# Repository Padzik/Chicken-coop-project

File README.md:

# Chicken coop project ("Kurník 21. století")
Chicken coop controller board (Eagle schematics) + arduino SW (for arduino and attiny + modified dependent libraries)

## HW comment
* Arduino nano + Attiny85 (for battery protection)
* LCD with nice user friendly menu
* External temp probe + automatic fan controller
* Set your GPS location (via menu) and you are ready to go! (actual Sunrise and Sunset is automaticly calculated every day + you can add user delay time)
* Build in Buzzer for Pavlov reflex (one minute before door open/close starts beeping)
* RTC has build in automatic SW correction (cheap RTCs can be running up to 30s late every day) + automatic summer/winter time
* External LED for door status + Data output via Serial 
* H-bridge + motor from screwdriver for door opening (build in safety mechanism for sensor failure) Door position is controlled by Magnetic Sensor Window Alarm Switch (I have tried mechanical and also Hall-sensor switches, but this one is more realible)
* It has also manual override function for doors
* Solar panel / main voltage power supply + UPS 6V battery (up to 2 days of running on battery backup) + Hibernation mode for low backup voltage on battery
* Double sided PCB can be easily prepared at home conditions (I have made many prototype versions)

Inspired by [Arduino chicken project by user RobotChicken](http://www.instructables.com/id/Arduino-Chicken-Coop-Controller/)

## Photos

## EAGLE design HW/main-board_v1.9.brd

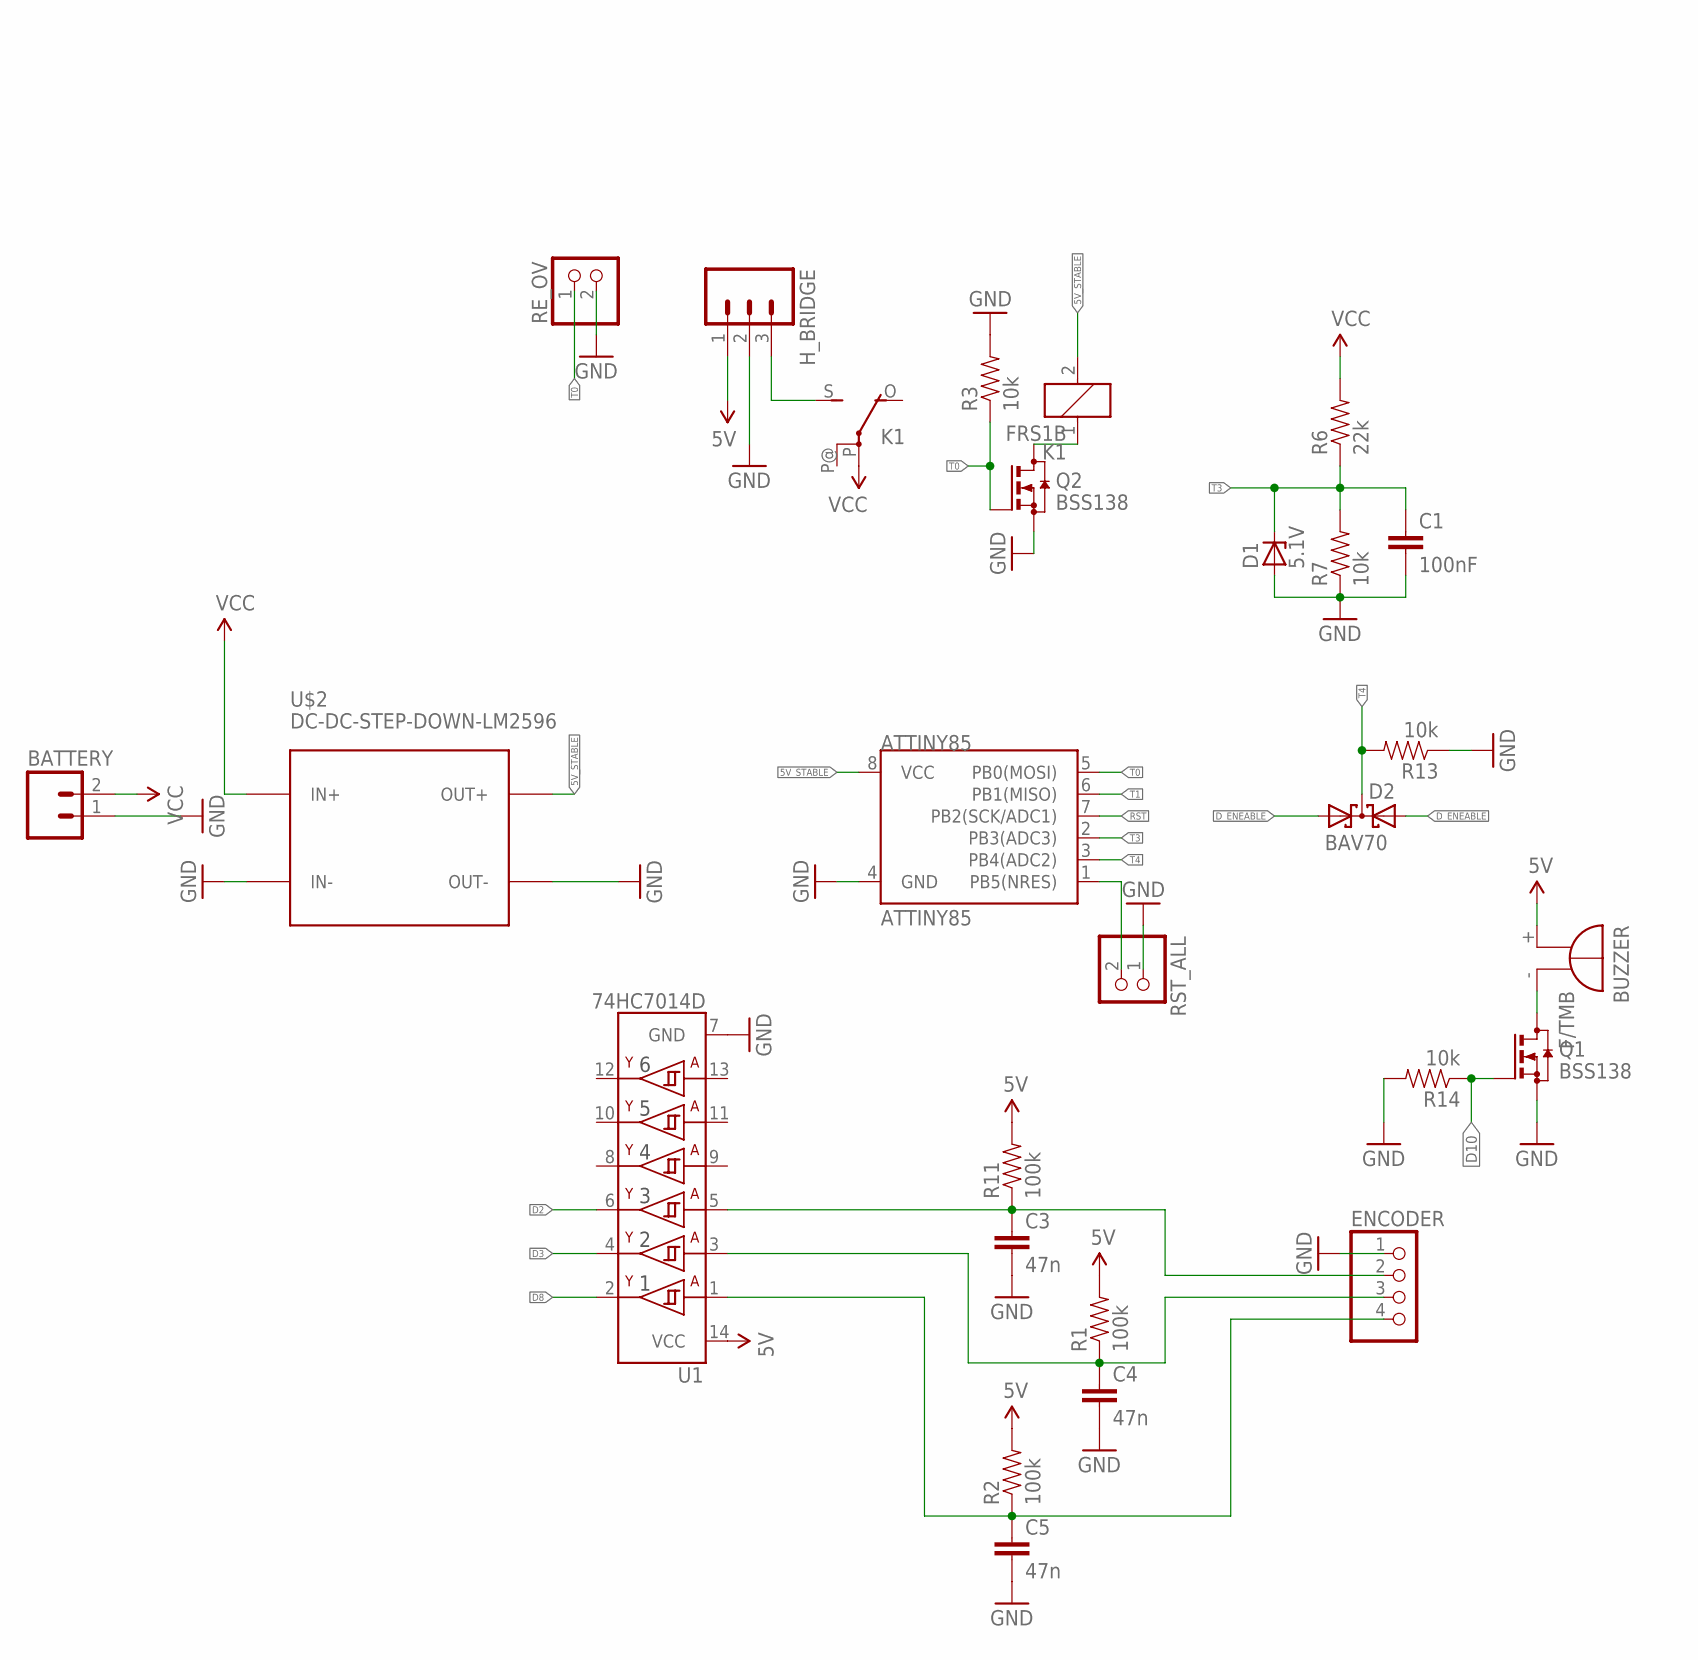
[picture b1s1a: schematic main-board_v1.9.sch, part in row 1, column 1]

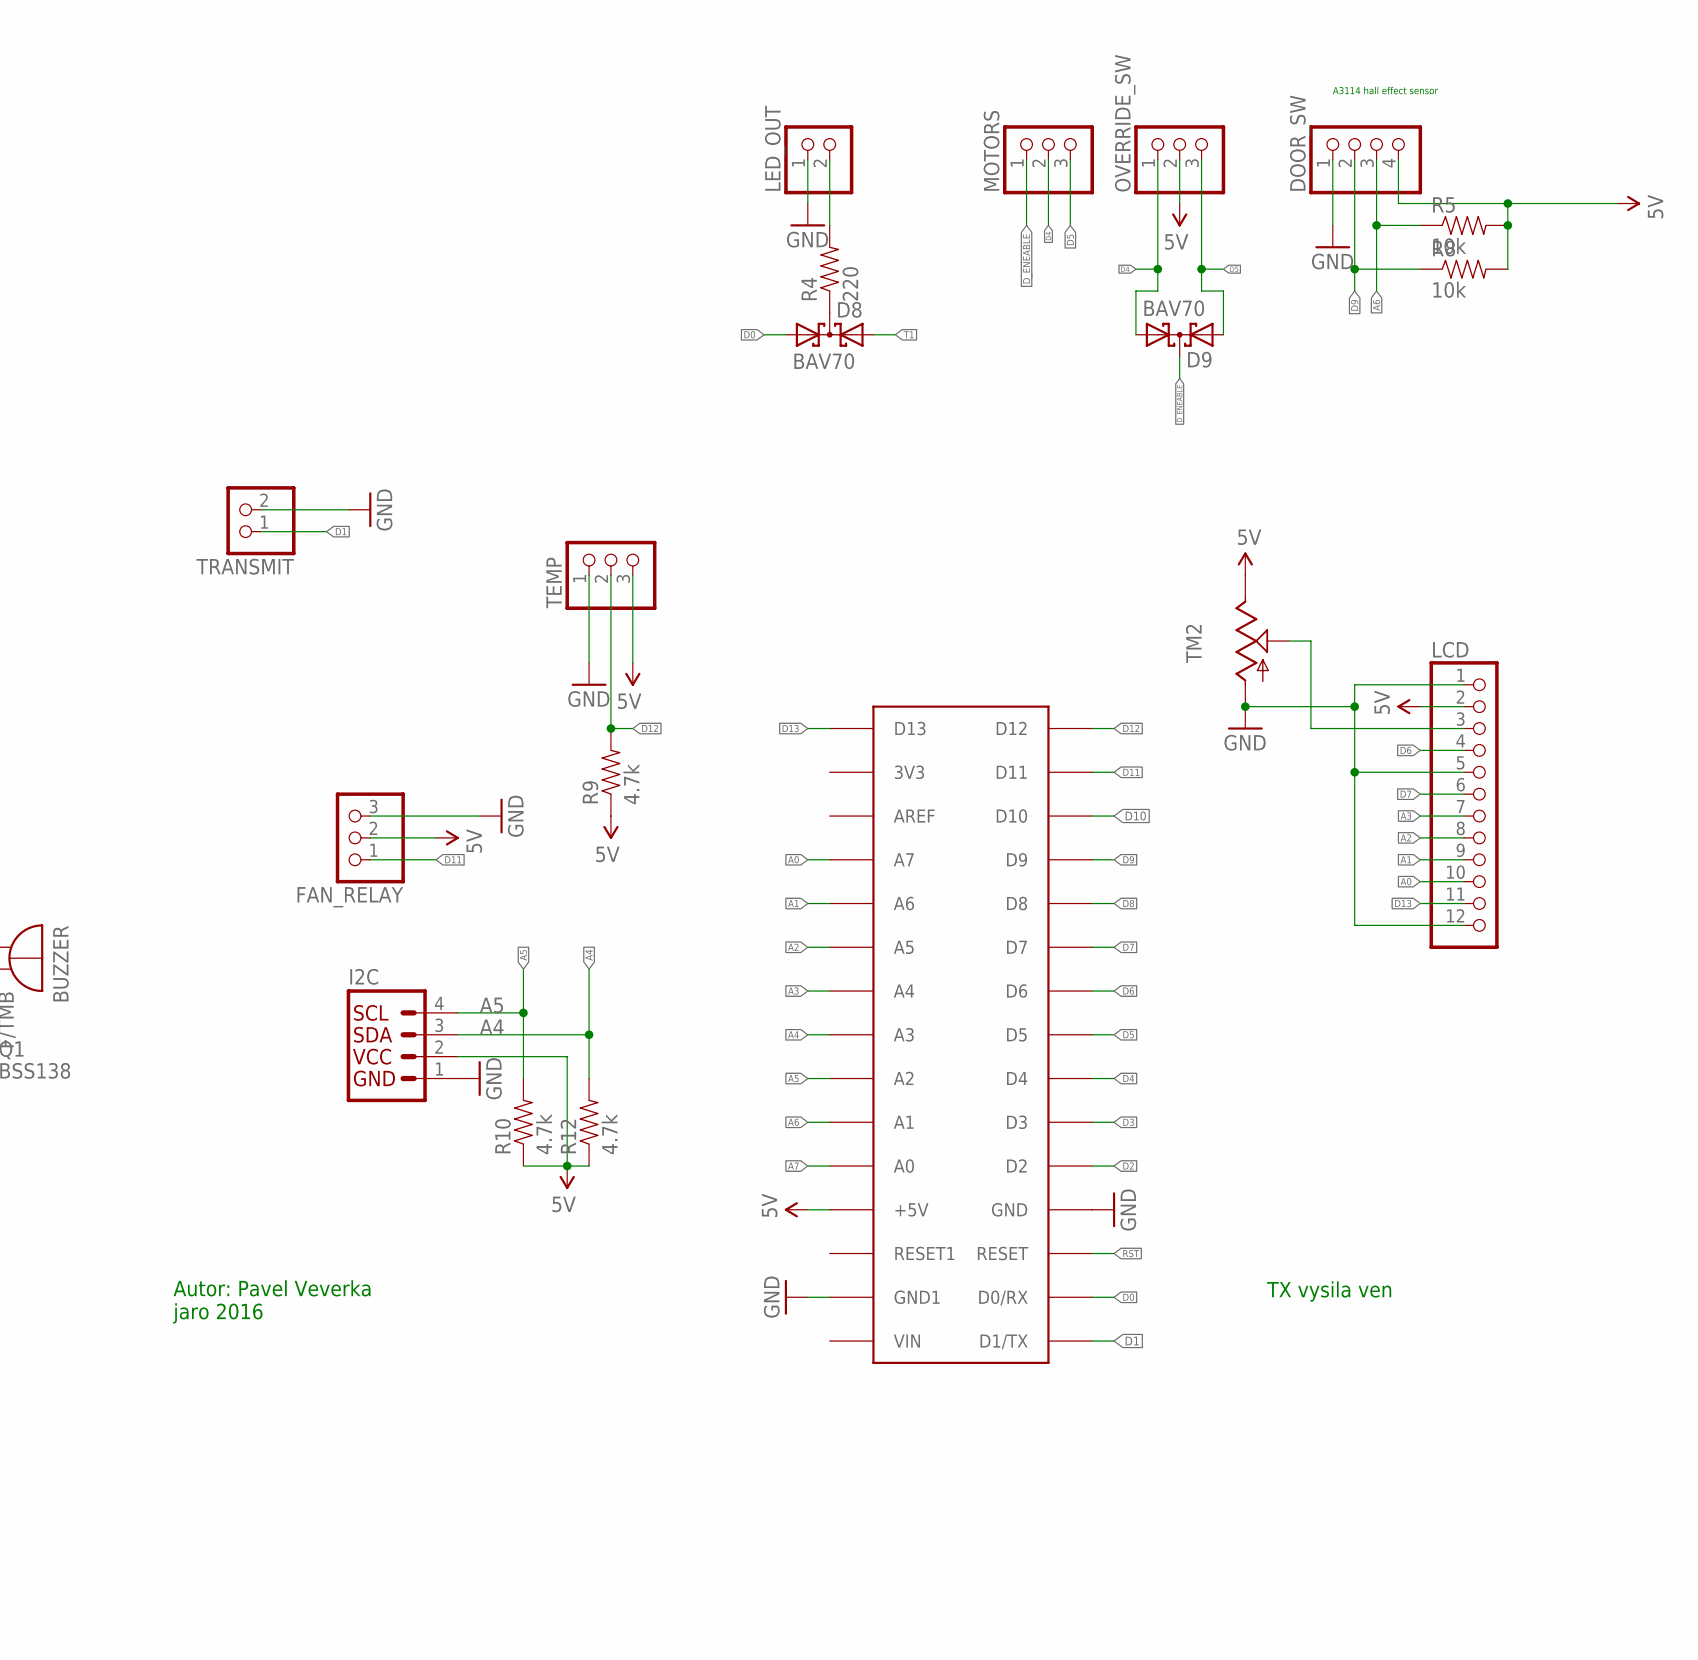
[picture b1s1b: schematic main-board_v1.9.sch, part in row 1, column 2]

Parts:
ATTINY85: ATTINY85; DIP08
BATTERY: M025MM; SCREWTERMINAL-5MM-2
BUZZER: F/TMB
C1: 100nF; CAP-PTH-5MM
C3, C4, C5: 47n; CAP-PTH-5MM
D1: 5.1V; ZDIO-7.5
D2, D8, D9: BAV70; SOT23
DOOR_SW: PINHD-1X4; 1X04
ENCODER: PINHD-1X4; 1X04
FAN_RELAY: PINHD-1X3; 1X03
H_BRIDGE: M03-SCREW-5MM; SCREWTERMINAL-5MM-3
I2C: I2C_STANDARD; 1X04
K1: FRS1B
LCD: PINHD-1X12; 1X12
LED_OUT: PINHD-1X2; 1X02
MOTORS: PINHD-1X3; 1X03
NANO: NANO; PDIP-32
OVERRIDE_SW: PINHD-1X3; 1X03
Q1, Q2: BSS138; SOT23
R1, R2, R11: 100k; 1206
R3, R5, R7, R8, R13, R14: 10k; 1206
R4: 220; 1206
R6: 22k; 1206
R9, R10, R12: 4.7k; 1206
RE_OV: PINHD-1X2; 1X02
RST_ALL: PINHD-1X2; 1X02
TEMP: PINHD-1X3; 1X03
TM2: TRIM; 6MM
TRANSMIT: PINHD-1X2; 1X02
U1: 74HC7014D; SOIC-14
U$2: DC-DC-STEP-DOWN-LM2596

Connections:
5V: BUZZER.+, DOOR_SW.4, FAN_RELAY.2, H_BRIDGE.1, I2C.2, LCD.2, NANO.+5V, OVERRIDE_SW.2, R1.2, R2.2, R5.2, R8.2, R9.1, R10.1, R11.2, R12.1, TEMP.3, TM2.E, U1.14 (VCC)
5V_STABLE: ATTINY85.8 (VCC), K1.2, U$2.OUT+
A0: LCD.10, NANO.A7
A1: LCD.9, NANO.A6
A2: LCD.8, NANO.A5
A3: LCD.7, NANO.A4
A4: I2C.3, NANO.A3, R12.2
A5: I2C.4, NANO.A2, R10.2
A6: DOOR_SW.3, NANO.A1, R5.1
A7: NANO.A0
AS: C4.1, ENCODER.3, R1.1, U1.3 (2A)
ASDF: C5.1, ENCODER.4, R2.1, U1.1 (1A)
D0: D8.1 (A1), NANO.D0/RX
D1: NANO.D1/TX, TRANSMIT.1
D2: NANO.D2, U1.6 (3Y)
D3: NANO.D3, U1.4 (2Y)
D4: D9.1 (A1), MOTORS.2, NANO.D4, OVERRIDE_SW.1
D5: D9.2 (A2), MOTORS.3, NANO.D5, OVERRIDE_SW.3
D6: LCD.4, NANO.D6
D7: LCD.6, NANO.D7
D8: NANO.D8, U1.2 (1Y)
D9: DOOR_SW.2, NANO.D9, R8.1
D10: NANO.D10, Q1.1 (G), R14.1
D11: FAN_RELAY.1, NANO.D11
D12: NANO.D12, R9.2, TEMP.2
D13: LCD.11, NANO.D13
DS: C3.1, ENCODER.2, R11.1, U1.5 (3A)
D_ENEABLE: D2.2 (A2), D9.3 (C), MOTORS.1
GND: ATTINY85.4 (GND), BATTERY.1, C1.2, C3.2, C4.2, C5.2, D1.A, DOOR_SW.1, ENCODER.1, FAN_RELAY.3, H_BRIDGE.2, I2C.1, LCD.1, LCD.5, LCD.12, LED_OUT.1, NANO.GND, NANO.GND1, Q1.2 (S), Q2.2 (S), R3.2, R7.1, R13.1, R14.2, RE_OV.2, RST_ALL.1, TEMP.1, TM2.A, TRANSMIT.2, U1.7 (GND), U$2.IN-, U$2.OUT-
unnamed: ATTINY85.1 (PB5(NRES)), RST_ALL.2
unnamed: H_BRIDGE.3, K1.S
unnamed: D8.3 (C), R4.1
unnamed: K1.1, Q2.3 (D)
unnamed: LED_OUT.2, R4.2
unnamed: LCD.3, TM2.S
unnamed: BUZZER.-, Q1.3 (D)
RST: ATTINY85.7 (PB2(SCK/ADC1)), NANO.RESET
T0: ATTINY85.5 (PB0(MOSI)), Q2.1 (G), R3.1, RE_OV.1
T1: ATTINY85.6 (PB1(MISO)), D8.2 (A2)
T3: ATTINY85.2 (PB3(ADC3)), C1.1, D1.C, R6.1, R7.2
T4: ATTINY85.3 (PB4(ADC2)), D2.3 (C), R13.2
VCC: BATTERY.2, K1.P, R6.2, U$2.IN+

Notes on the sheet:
Autor: Pavel Veverka jaro 2016
TX vysila ven
A3114 hall effect sensor

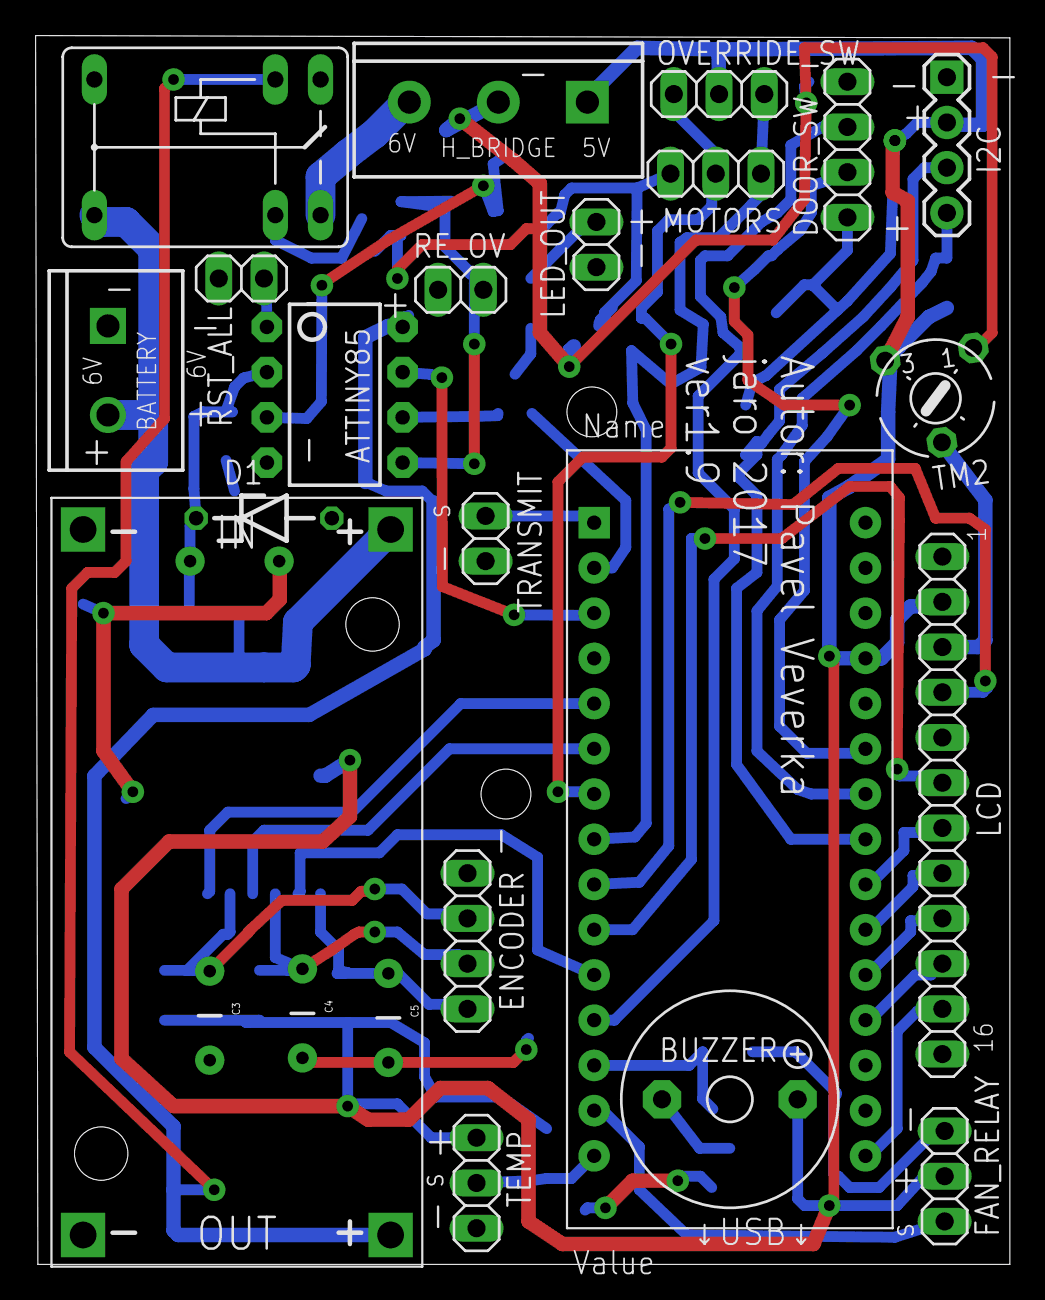
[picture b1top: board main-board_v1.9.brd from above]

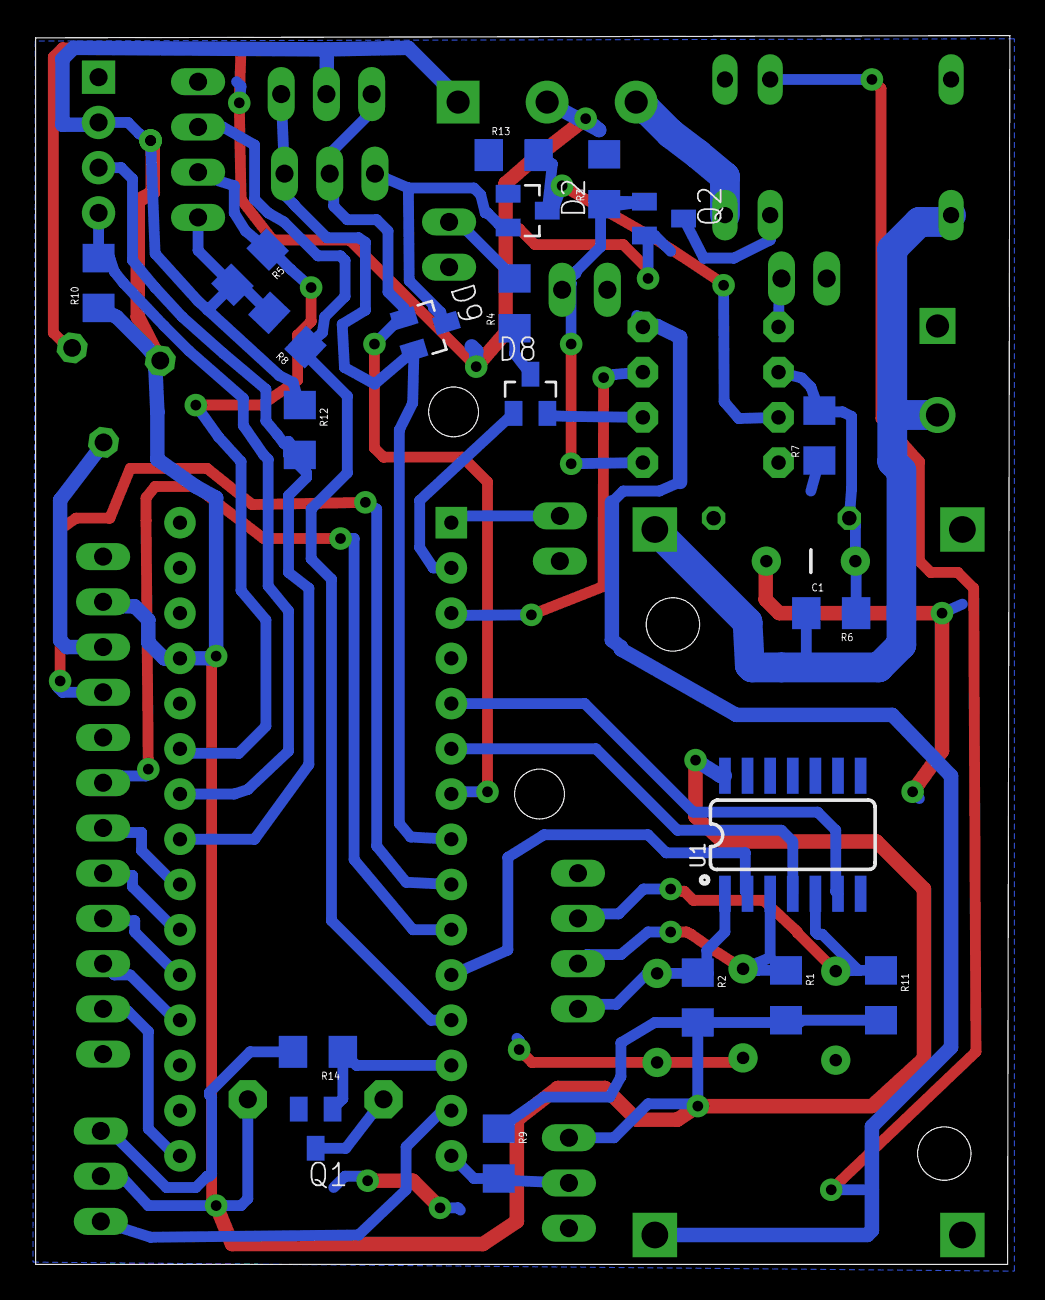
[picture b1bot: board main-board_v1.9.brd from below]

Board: 2 copper layers, 54.7 x 69.0 mm, 45 parts (21 on the bottom side), 41 nets.

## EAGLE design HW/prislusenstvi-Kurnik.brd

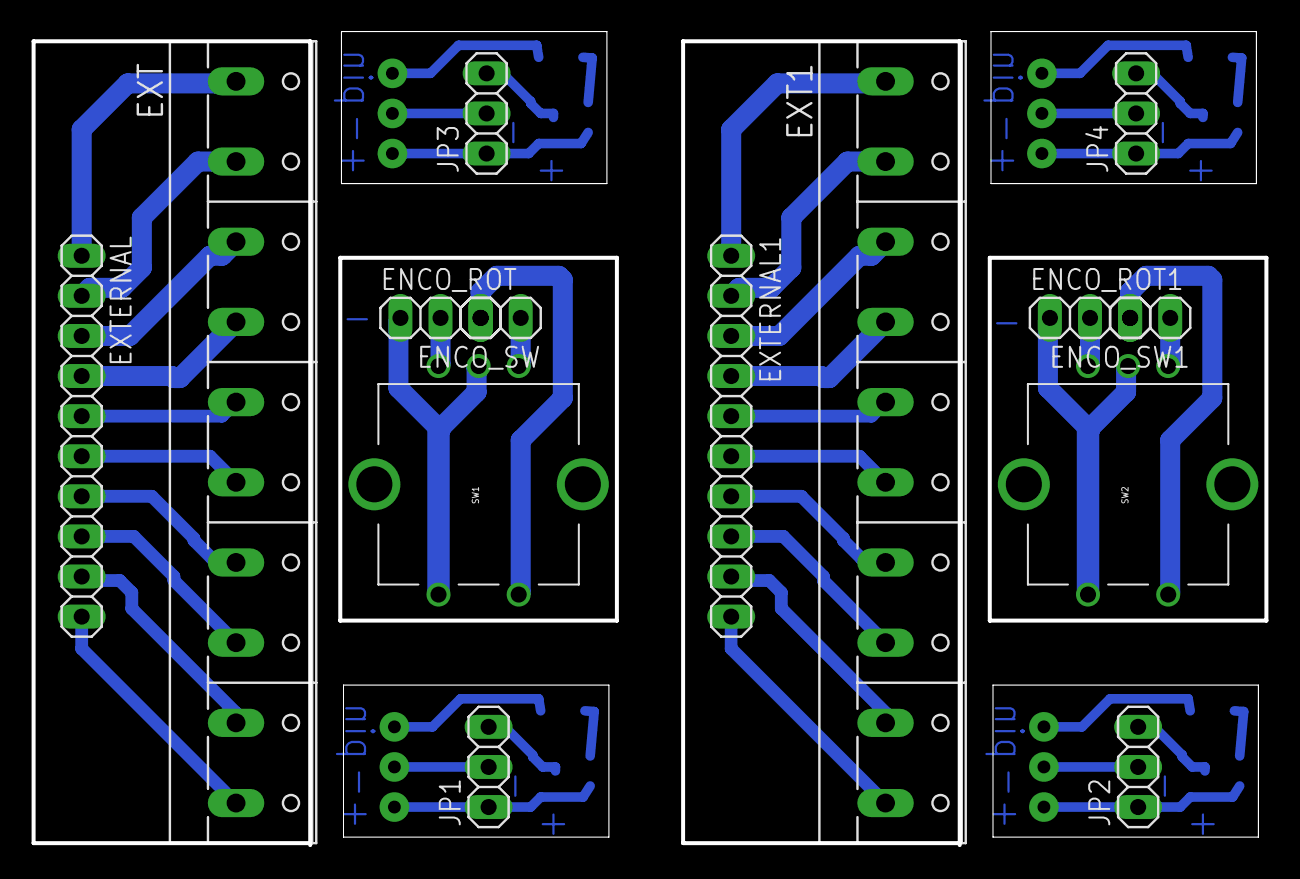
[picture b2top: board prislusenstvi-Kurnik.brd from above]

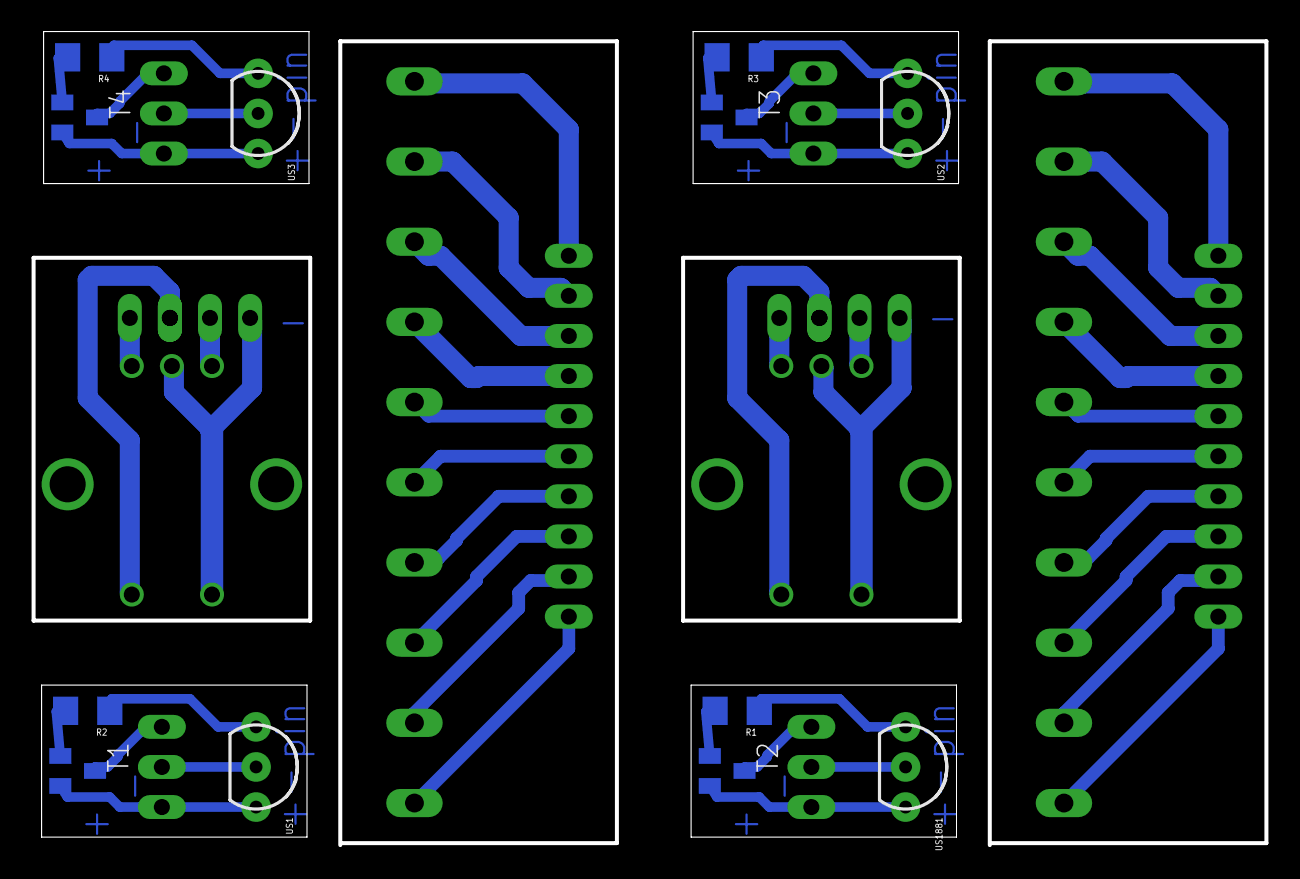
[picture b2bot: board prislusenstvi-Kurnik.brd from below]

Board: 2 copper layers, 78.1 x 51.5 mm, 26 parts (12 on the bottom side), 50 nets.

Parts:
ENCO_ROT, ENCO_ROT1: 1X03
ENCO_SW, ENCO_SW1: 1X02
EXT, EXT1: W237-10P
EXTERNAL, EXTERNAL1: 1X10
JP1, JP2, JP3, JP4: 1X03
R1, R2, R3, R4: 10k; 1206
SW1, SW2: ROTARTY_ENCODER; ROTARY_ENC_PLAIN
T1, T2, T3, T4: BC807-25; SOT23-BEC
US1, US2, US3, US1881: TO-92-AMMO

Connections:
5V: JP1.1, T2.E, US1881.3
5V1: JP2.1, T1.E, US1.3
5V2: JP3.1, T3.E, US2.3
5V3: JP4.1, T4.E, US3.3
E_BAT+: EXT.1, EXTERNAL.1
E_BAT+1: EXT1.1, EXTERNAL1.1
E_BAT-: EXT.2, EXTERNAL.2
E_BAT-1: EXT1.2, EXTERNAL1.2
E_DOOR1: EXT.7, EXTERNAL.7
E_DOOR2: EXT.8, EXTERNAL.8
E_DOOR3: EXT1.8, EXTERNAL1.8
E_DOOR4: EXT1.7, EXTERNAL1.7
E_GND: EXT.6, EXTERNAL.6
E_GND1: EXT1.6, EXTERNAL1.6
E_GND_T: EXT.10, EXTERNAL.10
E_GND_T1: EXT1.10, EXTERNAL1.10
E_LED+: EXT.5, EXTERNAL.5
E_LED+1: EXT1.5, EXTERNAL1.5
E_MOT+: EXT.3, EXTERNAL.3
E_MOT+1: EXT1.3, EXTERNAL1.3
E_MOT-: EXT.4, EXTERNAL.4
E_MOT-1: EXT1.4, EXTERNAL1.4
E_TEMP: EXT.9, EXTERNAL.9
E_TEMP1: EXT1.9, EXTERNAL1.9
GND: JP1.2, US1881.2
GND1: JP2.2, US1.2
GND2: JP3.2, US2.2
GND3: JP4.2, US3.2
unnamed: R1.2, T2.B
unnamed: R1.1, US1881.1
unnamed: ENCO_SW1.2, SW2.SW+
unnamed: ENCO_SW1.1, SW2.SW-
unnamed: R3.2, T3.B
unnamed: R3.1, US2.1
unnamed: ENCO_ROT1.2, SW2.C
unnamed: ENCO_ROT1.1, SW2.B
unnamed: ENCO_ROT1.3, SW2.A
unnamed: R2.2, T1.B
unnamed: R2.1, US1.1
unnamed: R4.2, T4.B
unnamed: R4.1, US3.1
unnamed: ENCO_SW.2, SW1.SW+
unnamed: ENCO_SW.1, SW1.SW-
unnamed: ENCO_ROT.2, SW1.C
unnamed: ENCO_ROT.1, SW1.B
unnamed: ENCO_ROT.3, SW1.A
PIN: JP1.3, T2.C
PIN1: JP2.3, T1.C
PIN2: JP3.3, T3.C
PIN3: JP4.3, T4.C

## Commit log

2018-06-12 :circus_tent: Added .gitattributes & .gitignore files
2018-06-12 V2.0
    V2.0
2018-06-12 Create README.md
    First readme
2018-06-12 Update README.md
    V2.0

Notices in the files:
parts and their libraries:
SparkFun-Capacitors: Licensing: Creative Commons ShareAlike 4.0 International - https://creativecommons.org/licenses/by-sa/4.0
diy-modules: Released under the Creative Commons Attribution 4.0 International License: http://creativecommons.org/licenses/by/4.0
